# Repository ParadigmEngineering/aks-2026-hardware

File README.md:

# aks-2026-hardware
Autonomous Karting Series (2026) hardware for Paradigm Engineering

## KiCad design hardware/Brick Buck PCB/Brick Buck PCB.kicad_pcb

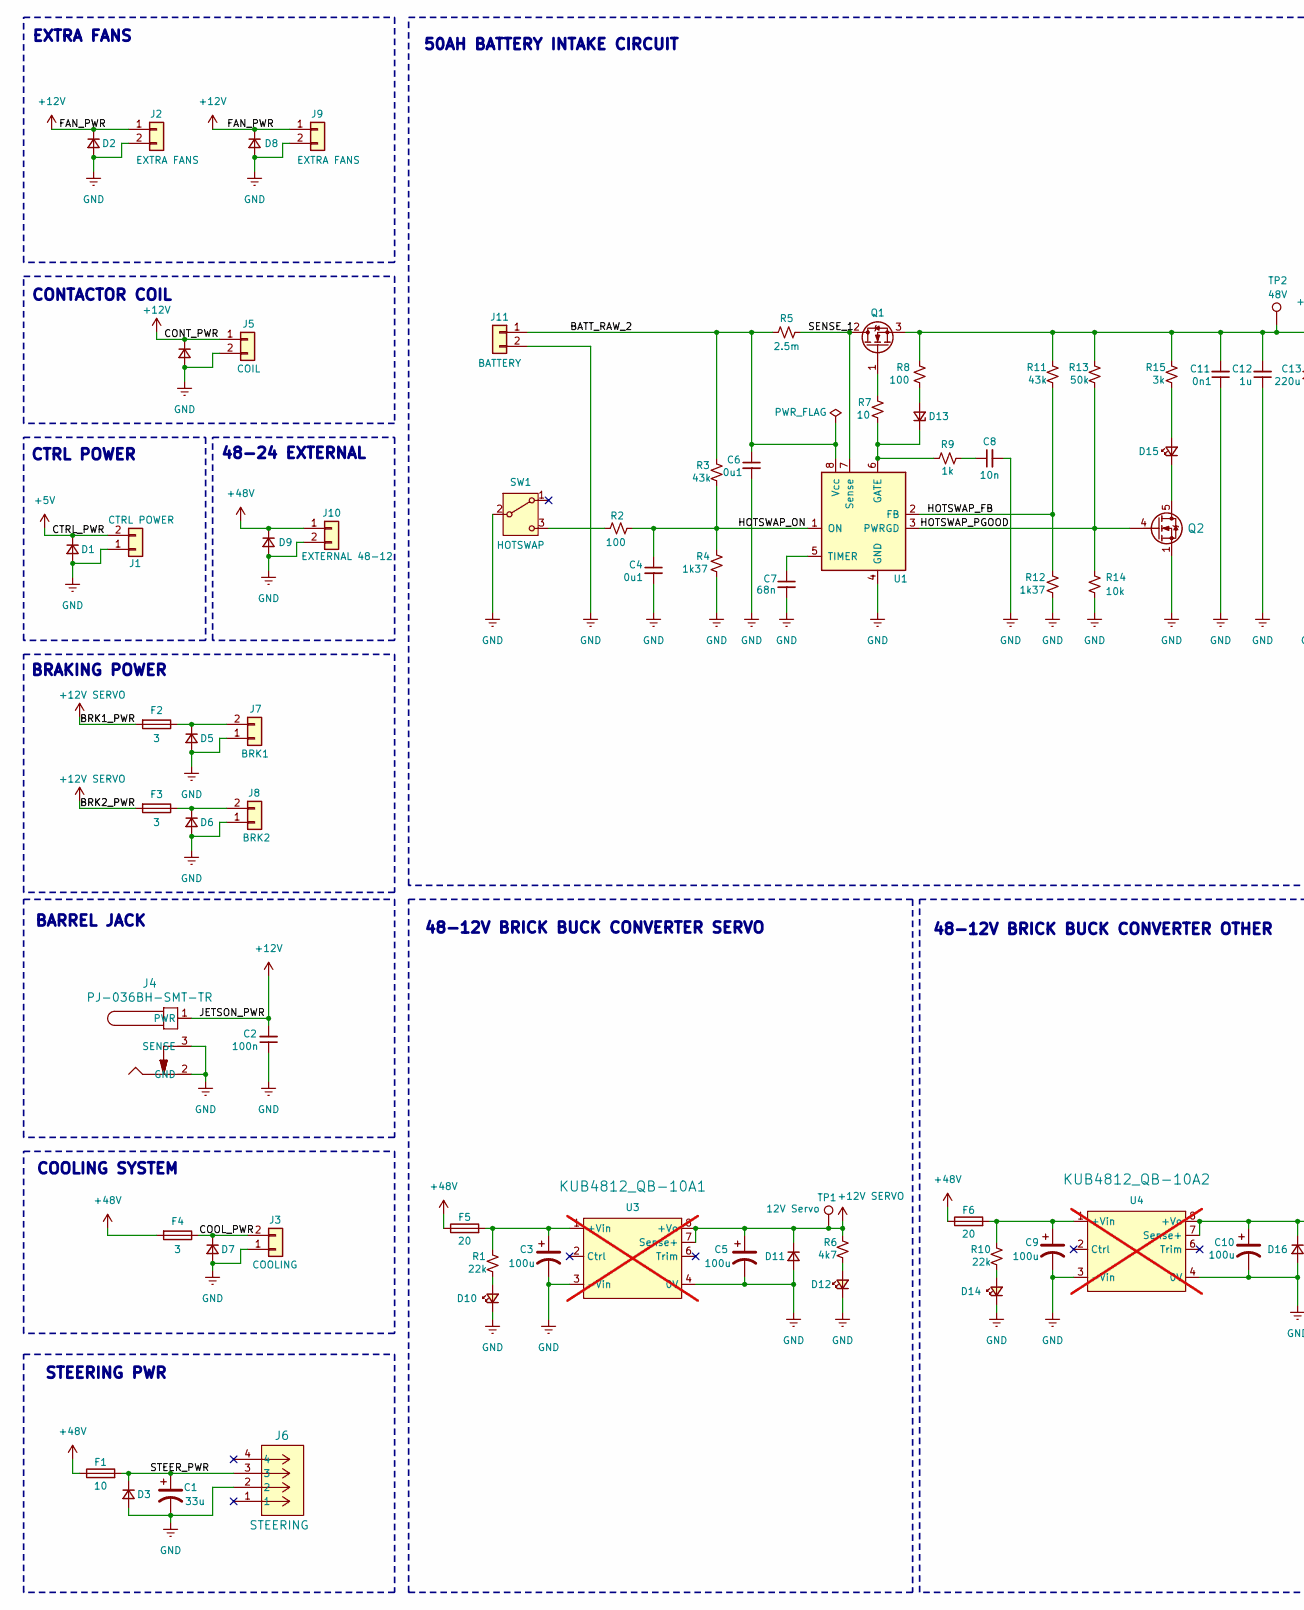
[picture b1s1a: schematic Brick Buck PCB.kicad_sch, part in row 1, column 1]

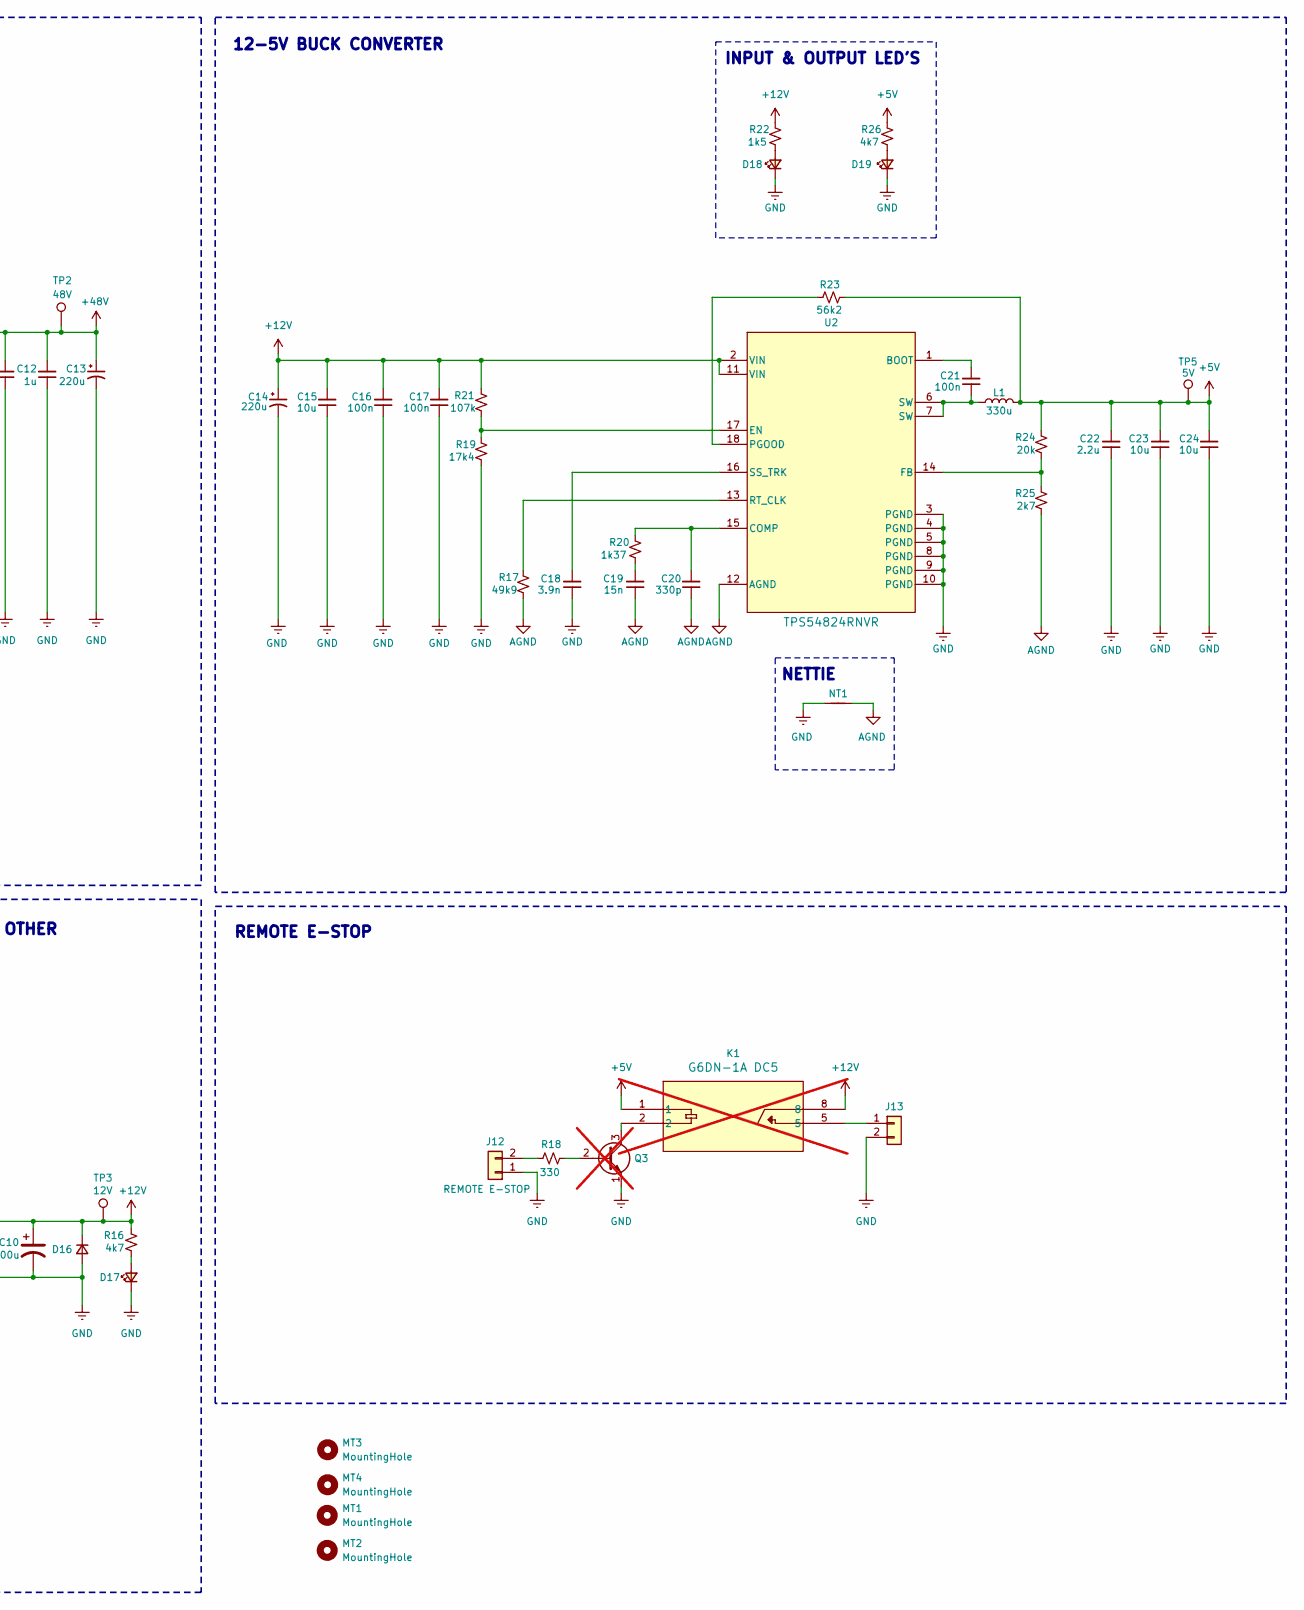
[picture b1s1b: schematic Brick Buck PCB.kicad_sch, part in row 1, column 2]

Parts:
C1: 33u; CP_Radial_D10.0mm_P5.00mm; Digikey 1189-2207-ND
C2: 100n; C_0402_1005Metric_Pad0.74x0.62mm_HandSolder
C3, C9: 100u; CAP_8 X 11.5_PAN
C4, C6: 0u1; C_0805_2012Metric_Pad1.18x1.45mm_HandSolder; Voltage 48V; LCSC 0.1u
C5, C10: 100u; CAPPRD200W50D500H1100
C7: 68n; C_0805_2012Metric_Pad1.18x1.45mm_HandSolder; Voltage 44V; LCSC 68n
C8: 10n; C_0805_2012Metric_Pad1.18x1.45mm_HandSolder; Voltage 68V; LCSC 10n
C11: 0n1; C_0805_2012Metric_Pad1.18x1.45mm_HandSolder; Voltage 48V
C12: 1u; C_0805_2012Metric_Pad1.18x1.45mm_HandSolder; Voltage 48V; LCSC 1u
C13: 220u; CP_Radial_D16.0mm_P7.50mm; Voltage 48V; Digikey 493-5867-ND
C14: 220u; CAPPRD350W60D800H1150
C15: 10u; C_1210_3225Metric_Pad1.33x2.70mm_HandSolder; MANUFACTURER PART NUMBER MSASU32MSB5106KPNA01
C16, C17: 100n; C_0603_1608Metric_Pad1.08x0.95mm_HandSolder; MANUFACTURER PART NUMBER C0603C104M3VACTU
C18: 3.9n; C_0201_0603Metric_Pad0.64x0.40mm_HandSolder; MANUFACTURER PART NUMBER GRM033R71A392KA01D
C19: 15n; C_0805_2012Metric_Pad1.18x1.45mm_HandSolder; MANUFACTURER PART NUMBER GRM2195C1H153JA01D
C20: 330p; C_0402_1005Metric_Pad0.74x0.62mm_HandSolder; MANUFACTURER PART NUMBER GRM1555C1H331JA01D
C21: 100n; C_0402_1005Metric_Pad0.74x0.62mm_HandSolder; MANUFACTURER PART NUMBER GRM155R71C104KA88D
C22: 2.2u; C_0805_2012Metric_Pad1.18x1.45mm_HandSolder; MANUFACTURER PART NUMBER GRM21BR71A225KA01L
C23, C24: 10u; C_0805_2012Metric_Pad1.18x1.45mm_HandSolder; MANUFACTURER PART NUMBER C0805C106K8PACTU
D1, D2, D3, D4, D5, D6, D7, D8, D9: 1655-S1GCT-ND; D_SMA; Digikey S1G
D10, D14, D19: KT-0603R; LED_KT-0603R; PARTREV 2013/01/24
D11, D16: SMDJ14A; DIOM6859X262N
D12, D17, D18: LED; LED_0603_1608Metric
D13: MMSZ5248B-HE3-08; D_SOD-123; Digikey MMSZ5248B-HE3-08GICT-ND
D15: LTST-C171GkT; LED_0805_2012Metric_Pad1.15x1.40mm_HandSolder
F1: 10; 3557-2; Digikey 3557-2
F2, F3, F4: 3; 3557-2; Digikey 36-3557-2-ND
F5, F6: 20; 3557-2
J1: CTRL POWER; Molex_Micro-Fit_3.0_43650-0200_1x02_P3.00mm_Horizontal; Digikey WM1860-ND
J2, J9: EXTRA FANS; Molex_Micro-Fit_3.0_43650-0215_1x02_P3.00mm_Vertical; Digikey WM1917-ND
J3: COOLING; Molex_Micro-Fit_3.0_43650-0200_1x02_P3.00mm_Horizontal; Digikey WM1860-ND
J4: PJ-036BH-SMT-TR; PJ036BHSMTTR
J5: COIL; Molex_Micro-Fit_3.0_43650-0215_1x02_P3.00mm_Vertical; Digikey WM1917-ND
J6: STEERING; CONN_SD-46207-001_04_MOL
J7: BRK1; Molex_Micro-Fit_3.0_43650-0200_1x02_P3.00mm_Horizontal; Digikey WM1860-ND
J8: BRK2; Molex_Micro-Fit_3.0_43650-0200_1x02_P3.00mm_Horizontal; Digikey WM1860-ND
J10: EXTERNAL 48-12; Molex_Micro-Fit_3.0_43650-0215_1x02_P3.00mm_Vertical; Digikey WM1917-ND
J11: BATTERY; Molex_Mini-Fit_Sr_42820-22XX_1x02_P10.00mm_Horizontal; Digikey WM11250-ND
J12: REMOTE E-STOP; Molex_KK-254_AE-6410-02A_1x02_P2.54mm_Vertical
J13: Conn_01x02; Molex_Micro-Fit_3.0_43650-0215_1x02_P3.00mm_Vertical
K1: G6DN-1A DC5; RELAY_G6DN-1A_OMR; not fitted
KUB4812_QB-10A1: U3; KUB48_QB-10A; not fitted
KUB4812_QB-10A2: U4; KUB48_QB-10A; not fitted
L1: 330u; SRN8040-3R3Y; Manufacturer_Part_Number SRN8040-3R3Y; Mouser Part Number 652-SRN8040-3R3Y
MT1, MT2, MT3, MT4: MountingHole; MountingHole_3.2mm_M3
NT1: NetTie1; NetTie-2_THT_Pad0.3mm
Q1: CSD19506KTT; TO-263-2; Digikey 296-49604-1-ND
Q2: CSD18543Q3A; VSON-8_3.3x3.3mm_P0.65mm_NexFET
Q3: 2N7000; TO92254P458H750-3; not fitted
R1, R10: 22k; R_0805_2012Metric_Pad1.20x1.40mm_HandSolder
R2, R8: 100; R_0805_2012Metric_Pad1.20x1.40mm_HandSolder; LCSC 100
R3, R11: 43k; R_0805_2012Metric_Pad1.20x1.40mm_HandSolder; LCSC 43K
R4, R12: 1k37; R_0805_2012Metric_Pad1.20x1.40mm_HandSolder; LCSC 1.37K
R5: 2.5m; R_2512_6332Metric_Pad1.40x3.35mm_HandSolder; Digikey_2.5m WSLF25121L300FEA
R6, R16, R26: 4k7; R_0805_2012Metric_Pad1.20x1.40mm_HandSolder
R7: 10; R_0805_2012Metric_Pad1.20x1.40mm_HandSolder; LCSC 10
R9: 1k; R_0805_2012Metric_Pad1.20x1.40mm_HandSolder; LCSC 1K
R13: 50k; R_0805_2012Metric_Pad1.20x1.40mm_HandSolder; LCSC 50k
R14: 10k; R_0805_2012Metric_Pad1.20x1.40mm_HandSolder; LCSC 10k
R15: 3k; R_0805_2012Metric_Pad1.20x1.40mm_HandSolder; LCSC 3k
R17: 49k9; R_0402_1005Metric_Pad0.72x0.64mm_HandSolder; MANUFACTURER PART NUMBER CRCW040249K9FKED
R18: 330; R_0402_1005Metric
R19: 17k4; R_0603_1608Metric_Pad0.98x0.95mm_HandSolder; MANUFACTURER PART NUMBER FRC0603F1742TS
R20: 1k37; R_0402_1005Metric_Pad0.72x0.64mm_HandSolder; MANUFACTURER PART NUMBER CRCW04021K37FKED
R21: 107k; R_0603_1608Metric_Pad0.98x0.95mm_HandSolder; MANUFACTURER PART NUMBER CRCW0402107KFKED
R22: 1k5; R_0805_2012Metric_Pad1.20x1.40mm_HandSolder
R23: 56k2; R_0402_1005Metric_Pad0.72x0.64mm_HandSolder; MANUFACTURER PART NUMBER RT0402FRE0756K2L
R24: 20k; R_0603_1608Metric_Pad0.98x0.95mm_HandSolder; MANUFACTURER PART NUMBER CRCW040220K0FKED
R25: 2k7; R_0603_1608Metric_Pad0.98x0.95mm_HandSolder; MANUFACTURER PART NUMBER CRCW04022K74FKED
SW1: HOTSWAP; SW_EG1218; Digikey EG1903-ND
TP1: 12V Servo; TestPoint_Pad_D2.5mm
TP2: 48V; TestPoint_Pad_D2.5mm
TP3: 12V; TestPoint_Pad_D2.5mm
TP5: 5V; TestPoint_Pad_D2.5mm
U1: LT1641-1CS8#TRPBF; SOIC-8_3.9x4.9mm_P1.27mm; Digikey LT1641-1
U2: TPS54824RNVR; RNV0018B

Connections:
+5V: C22.2, C23.2, C24.2, D1.1 (K), J1.2, K1.1, L1.2, R23.2, R24.2, R26.2, TP5.1; also elsewhere on the board
+12V: C2.2, C10.P, C14.P, C15.2, C16.2, C17.2, D2.1 (K), D4.1 (K), D8.1 (K), D16.C (K), J2.1, J4.1 (PWR), J5.1, J9.1, K1.8, KUB4812_QB-10A2.7 (Sense+), KUB4812_QB-10A2.8 (+Vo), R16.2, R21.1, R22.1, TP3.1 (1_1), U2.2 (VIN), U2.11 (VIN)
+12V SERVO: C5.P, D11.C (K), F2.2, F3.2, KUB4812_QB-10A1.7 (Sense+), KUB4812_QB-10A1.8 (+Vo), R6.2, TP1.1 (1_1)
+48V: C11.2, C12.2, C13.1, D9.1 (K), F1.1, F4.2, F5.1, F6.1, J10.1, Q1.3 (S), R8.2, R11.1, R13.1, R15.1, TP2.1 (1_1)
/BATT_RAW_2: C6.1, J11.1, R3.1, R5.2, U1.8 (Vcc)
/COOL_PWR: D7.1 (K), F4.1, J3.2
/HOTSWAP_FB: R11.2, R12.1, U1.2 (FB)
/HOTSWAP_ON: C4.1, R2.1, R3.2, R4.1, U1.1 (ON)
/HOTSWAP_PGOOD: Q2.4 (G), R13.2, R14.1, U1.3 (PWRGD)
/SENSE_1: Q1.2 (D), R5.1, U1.7 (Sense)
/STEER_PWR: C1.1, D3.1 (K), F1.2, J6.3
AGND: C19.1, C20.1, NT1.2, R17.1, R25.1, U2.12 (AGND)
GND: C1.2, C2.1, C3.2, C4.2, C5.N, C6.2, C7.2, C8.2, C9.2, C10.N, C11.1, C12.1, C13.2, C14.N, C15.1, C16.1, C17.1, C18.1, C22.1, C23.1, C24.1, D1.2 (A), D2.2 (A), D3.2 (A), D4.2 (A), D5.2 (A), D6.2 (A), D7.2 (A), D8.2 (A), D9.2 (A), D10.C (K), D11.A, D12.1 (K), D14.C (K), D16.A, D17.1 (K), D18.1 (K), D19.C (K), J1.1, J2.2, J3.1, J4.2 (GND), J4.3 (SENSE), J5.2, J6.2, J7.1, J8.1, J9.2, J10.2, J11.2, J12.1, J13.2, KUB4812_QB-10A1.3 (-Vin), KUB4812_QB-10A1.4 (0V), KUB4812_QB-10A2.3 (-Vin), KUB4812_QB-10A2.4 (0V), NT1.1, Q2.1 (S), Q2.2 (S), Q2.3 (S), Q3.1 (E), R4.2, R12.2, R14.2, R19.2, SW1.2 (B), U1.4 (GND), U2.3 (PGND), U2.4 (PGND), U2.5 (PGND), U2.8 (PGND), U2.9 (PGND), U2.10 (PGND)
unnamed: C8.1, R9.1
unnamed: C19.2, R20.1
unnamed: C21.1, L1.1, U2.6 (SW), U2.7 (SW)
unnamed: D5.1 (K), F2.1, J7.2
unnamed: D6.1 (K), F3.1, J8.2
unnamed: D10.A, R1.1
unnamed: D12.2 (A), R6.1
unnamed: D13.2 (A), R8.1
unnamed: D13.1 (K), R7.2, R9.2, U1.6 (GATE)
unnamed: D14.A, R10.1
unnamed: D15.2 (A), R15.2
unnamed: D15.1 (K), Q2.5 (D)
unnamed: D17.2 (A), R16.1
unnamed: D18.2 (A), R22.2
unnamed: D19.A, R26.1
unnamed: J12.2, R18.1
unnamed: J13.1, K1.5
unnamed: C3.1, F5.2, KUB4812_QB-10A1.1 (+Vin), R1.2
unnamed: C9.1, F6.2, KUB4812_QB-10A2.1 (+Vin), R10.2
unnamed: Q1.1 (G), R7.1
unnamed: Q3.2 (B), R18.2
unnamed: K1.2, Q3.3 (C)
unnamed: R2.2, SW1.3 (C)
unnamed: C7.1, U1.5 (TIMER)
unnamed: C21.2, U2.1 (BOOT)
unnamed: C20.2, R20.2, U2.15 (COMP)
unnamed: R19.1, R21.2, U2.17 (EN)
unnamed: R24.1, R25.2, U2.14 (FB)
unnamed: R23.1, U2.18 (PGOOD)
unnamed: R17.2, U2.13 (RT_CLK)
unnamed: C18.2, U2.16 (SS_TRK)

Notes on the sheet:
NETTIE
50AH BATTERY INTAKE CIRCUIT
CTRL POWER
48-12V BRICK BUCK CONVERTER SERVO
BARREL JACK
INPUT & OUTPUT LED'S
48-24 EXTERNAL
48-12V BRICK BUCK CONVERTER OTHER
CONTACTOR COIL
REMOTE E-STOP
COOLING SYSTEM
12-5V BUCK CONVERTER
BRAKING POWER
EXTRA FANS
STEERING PWR

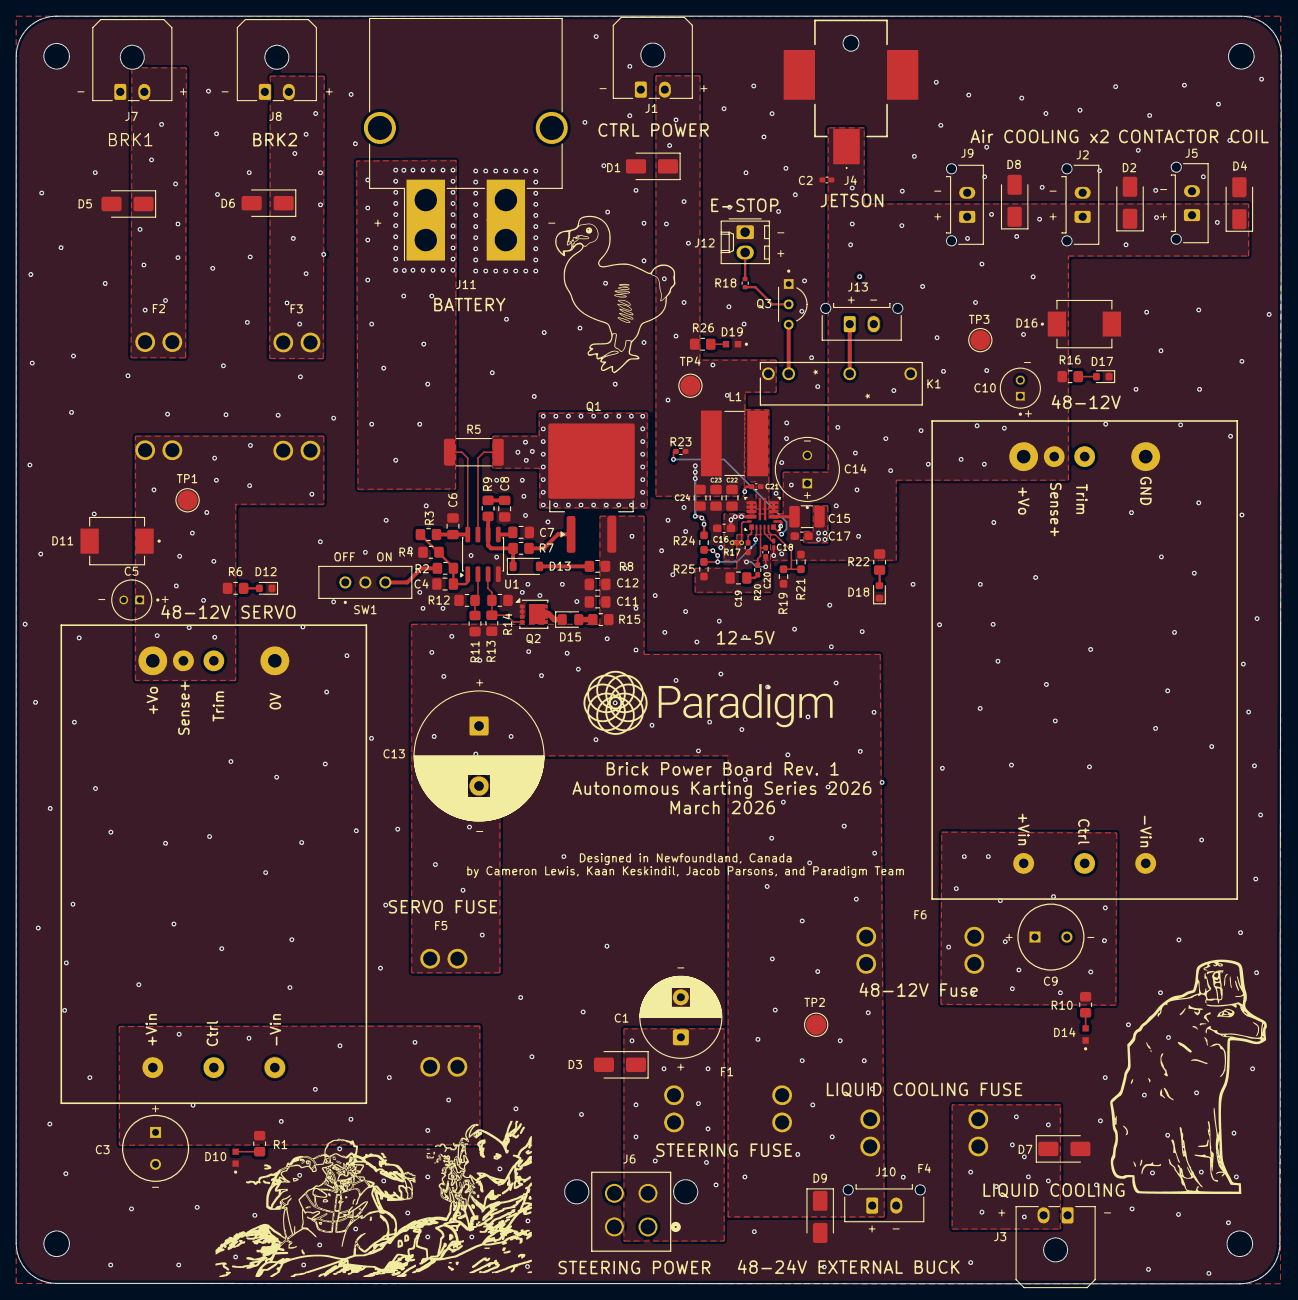
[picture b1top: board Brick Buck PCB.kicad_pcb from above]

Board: 4 copper layers, 158.0 x 158.3 mm, 107 parts (0 on the bottom side), 44 nets.

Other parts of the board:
TP4: 5V; TestPoint_Pad_D2.5mm

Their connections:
+5V: TP4.1 (1_1); also elsewhere on the board

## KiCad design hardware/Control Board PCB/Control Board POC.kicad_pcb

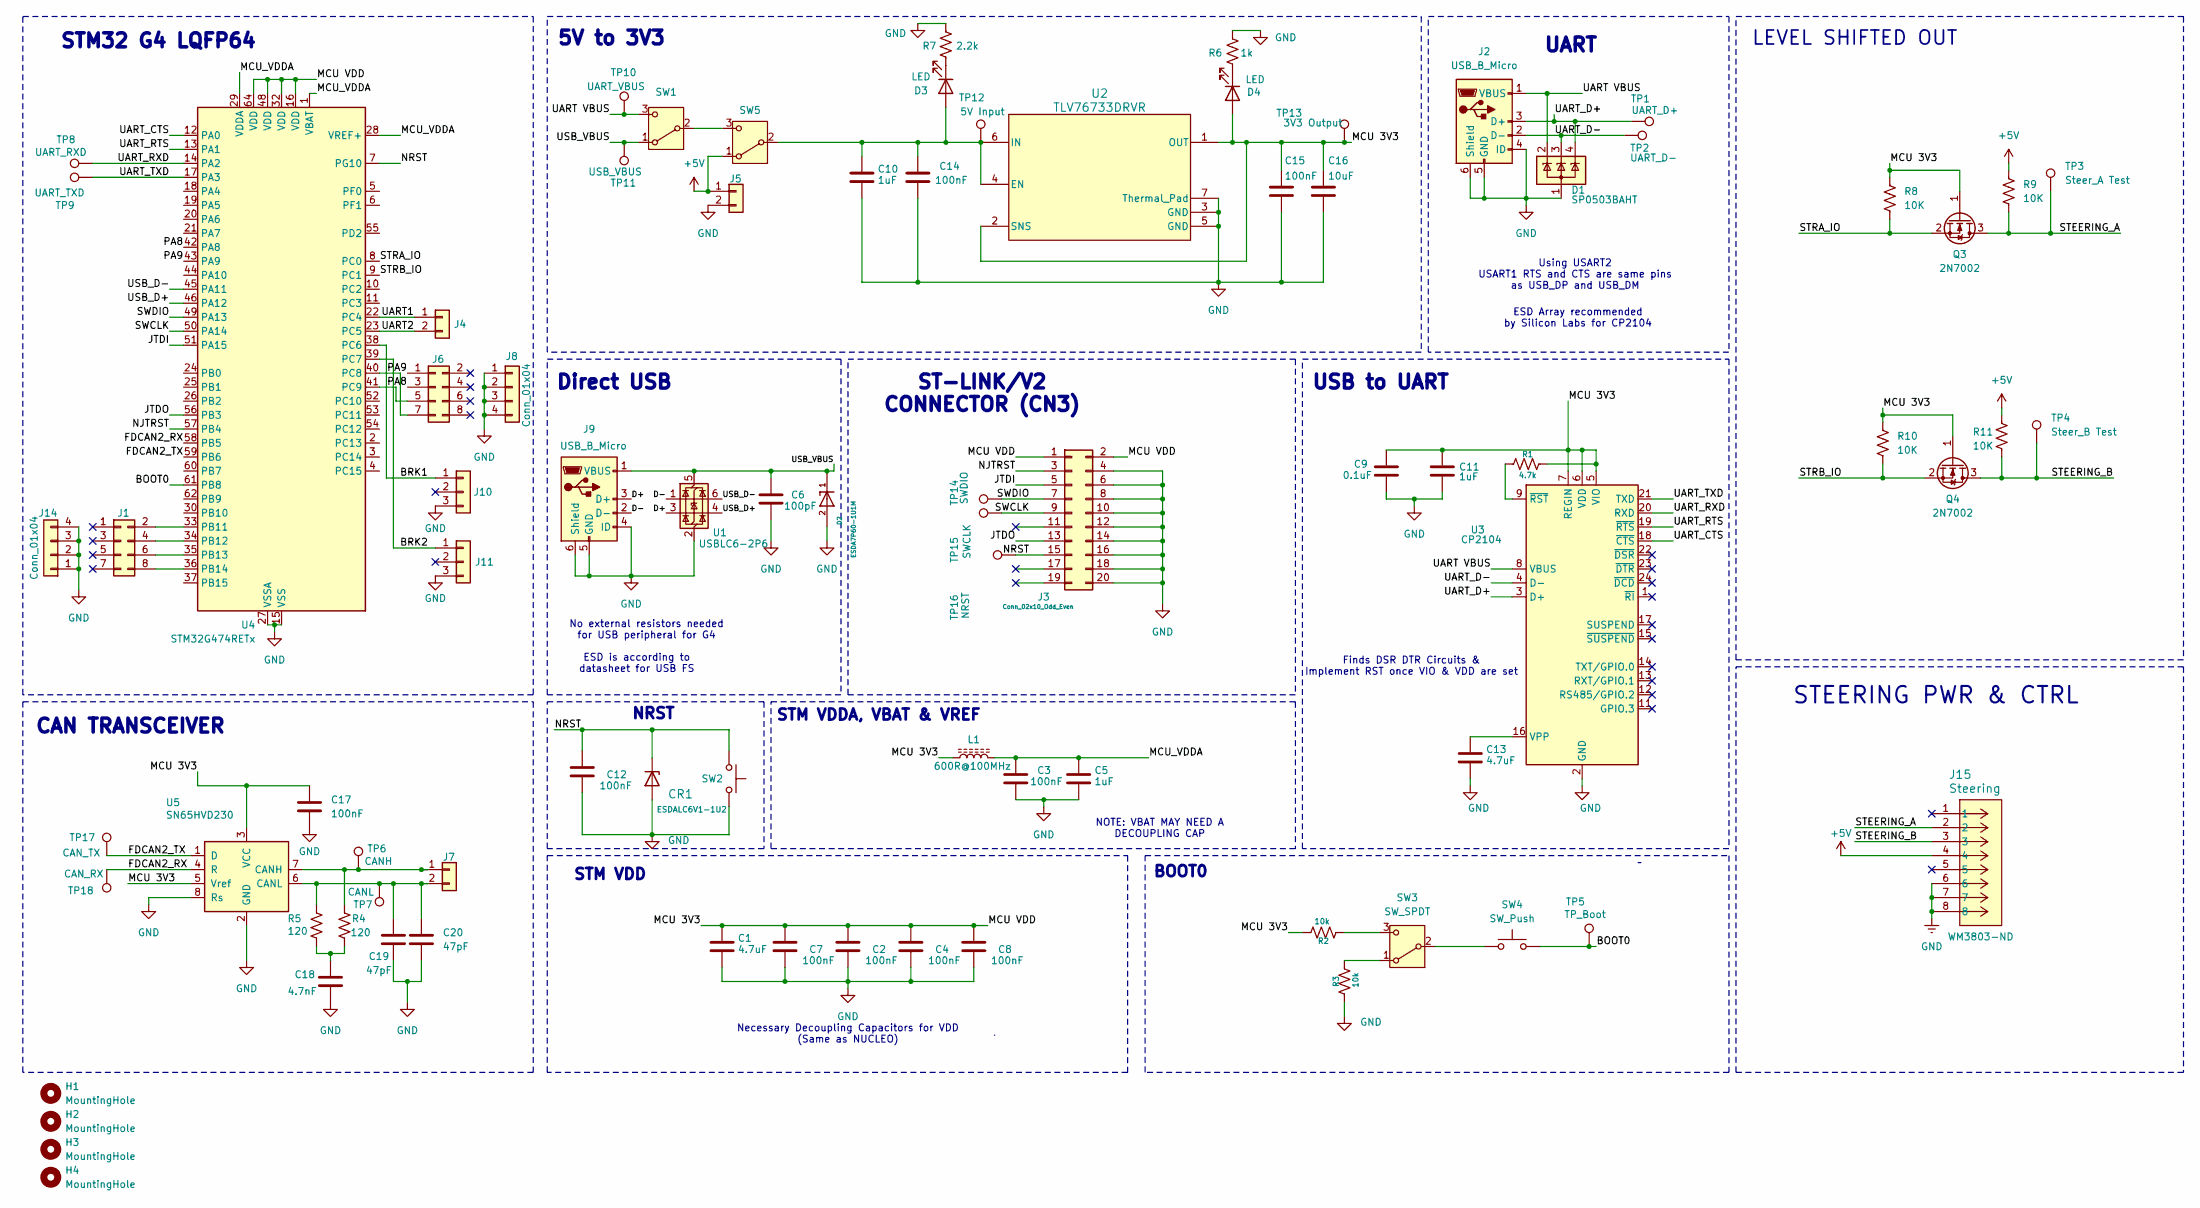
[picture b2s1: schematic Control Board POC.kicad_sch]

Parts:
C1, C13: 4.7uF; C_0402_1005Metric_Pad0.74x0.62mm_HandSolder
C2, C3, C4, C7, C8, C12, C14, C15: 100nF; C_0402_1005Metric_Pad0.74x0.62mm_HandSolder
C5, C10, C11: 1uF; C_0402_1005Metric_Pad0.74x0.62mm_HandSolder
C6: 100pF; C_0402_1005Metric_Pad0.74x0.62mm_HandSolder
C9: 0.1uF; C_0402_1005Metric_Pad0.74x0.62mm_HandSolder
C16: 10uF; C_0402_1005Metric_Pad0.74x0.62mm_HandSolder
C17: 100nF; C_0402_1005Metric
C18: 4.7nF; C_0402_1005Metric
C19, C20: 47pF; C_0402_1005Metric
CR1: ESDALC6V1-1U2; DIODE_ESDALC6V1-1U2
D1: SP0503BAHT; SOT-143
D2: ESDA7P60-1U1M; TVS_ESDA7P60-1U1M; PARTREV 4
D3: LED; LED_0603_1608Metric
D4: LED; LED_0805_2012Metric
H1, H2, H3, H4: MountingHole; MountingHole_3.2mm_M3
J1, J6: Conn_02x04_Odd_Even; PinHeader_2x04_P2.54mm_Vertical
J2, J9: USB_B_Micro; USB_Micro-B_Amphenol_10118194_Horizontal
J3: Conn_02x10_Odd_Even; PinHeader_2x10_P2.54mm_Vertical
J4, J5: Conn_01x02; PinHeader_1x02_P2.54mm_Vertical
J7: Conn_01x02; CONN_SD-43650-010_02_MOL
J8, J14: Conn_01x04; PinHeader_1x04_P2.54mm_Vertical
J10, J11: Conn_01x03; PinHeader_1x03_P2.54mm_Vertical
J15: Steering; CONN_5566-08_MOL; Digikey WM3803-ND
L1: 600R@100MHz; L_0805_2012Metric
Q3, Q4: 2N7002; SOT-23
R1: 4.7k; R_0201_0603Metric
R2, R3: 10k; R_0201_0603Metric
R4, R5: 120; R_0201_0603Metric
R6: 1k; R_0201_0603Metric
R7: 2.2k; R_0201_0603Metric
R8, R9, R10, R11: 10K; R_0805_2012Metric_Pad1.20x1.40mm_HandSolder
SW1, SW3, SW5: SW_SPDT; SW_EG1218
SW2, SW4: SW_Push; PTS636SK25FSMTRLFS
TP1: UART_D+; TestPoint_Pad_D1.0mm
TP2: UART_D-; TestPoint_Pad_D1.0mm
TP3: Steer_A Test; TestPoint_Pad_D1.0mm
TP4: Steer_B Test; TestPoint_Pad_D1.0mm
TP5: TP_Boot; TestPoint_Pad_D1.0mm
TP6: CANH; TestPoint_Pad_D1.0mm
TP7: CANL; TestPoint_Pad_D1.0mm
TP8: UART_RXD; TestPoint_Pad_D1.0mm
TP9: UART_TXD; TestPoint_Pad_D1.0mm
TP10: UART_VBUS; TestPoint_Pad_D1.0mm
TP11: USB_VBUS; TestPoint_Pad_D1.0mm
TP12: 5V Input; TestPoint_Pad_D1.0mm
TP13: 3V3 Output; TestPoint_Pad_D1.0mm
TP14: SWDIO; TestPoint_Pad_D1.0mm
TP15: SWCLK; TestPoint_Pad_D1.0mm
TP16: NRST; TestPoint_Pad_D1.0mm
TP17: CAN_TX; TestPoint_Pad_D1.0mm
TP18: CAN_RX; TestPoint_Pad_D1.0mm
U1: USBLC6-2P6; SOT-666
U2: TLV76733DRVR; DRV0006A-IPC_B
U3: CP2104; QFN-24-1EP_4x4mm_P0.5mm_EP2.6x2.6mm
U4: STM32G474RETx; LQFP-64_10x10mm_P0.5mm
U5: SN65HVD230; SOIC-8_3.9x4.9mm_P1.27mm

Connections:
+5V: J5.1, J15.4, R9.1, R11.1, SW5.1 (A)
/BOOT0: SW4.2, TP5.1, U4.61 (PB8)
/BRK1: J10.1, U4.38 (PC6)
/BRK2: J11.1, U4.39 (PC7)
/D+: J9.3 (D+), U1.3 (I/O2)
/D-: J9.2 (D-), U1.1 (I/O1)
/FDCAN2_RX: TP18.1, U4.58 (PB5), U5.4 (R)
/FDCAN2_TX: TP17.1, U4.59 (PB6), U5.1 (D)
/JTDI: J3.5, U4.51 (PA15)
/JTDO: J3.13, U4.56 (PB3)
/MCU 3V3: C1.1, C2.1, C4.1, C7.1, C8.1, C9.2, C11.1, C15.1, C16.1, C17.1, D4.2 (A), J3.1, J3.2, L1.1, Q3.1 (G), Q4.1 (G), R1.2, R2.2, R8.1, R10.1, TP13.1, U2.1 (OUT), U2.2 (SNS), U3.5 (VIO), U3.6 (VDD), U3.7 (REGIN), U4.16 (VDD), U4.32 (VDD), U4.48 (VDD), U4.64 (VDD), U5.3 (VCC), U5.5 (Vref)
/MCU_VDDA: C3.1, C5.1, L1.2, U4.1 (VBAT), U4.28 (VREF+), U4.29 (VDDA)
/NJTRST: J3.3, U4.57 (PB4)
/NRST: C12.1, CR1.1 (K), J3.15, SW2.1, TP16.1, U4.7 (PG10)
/PA8: J6.3, U4.42 (PA8)
/PA9: J6.1, U4.43 (PA9)
/STEERING_A: J15.2, Q3.3 (D), R9.2, TP3.1
/STEERING_B: J15.3, Q4.3 (D), R11.2, TP4.1
/STRA_IO: Q3.2 (S), R8.2, U4.8 (PC0)
/STRB_IO: Q4.2 (S), R10.2, U4.9 (PC1)
/SWCLK: J3.9, TP15.1, U4.50 (PA14)
/SWDIO: J3.7, TP14.1, U4.49 (PA13)
/UART1: J4.1, U4.22 (PC4)
/UART2: J4.2, U4.23 (PC5)
/UART VBUS: D1.2 (K), J2.1 (VBUS), SW1.3 (C), TP10.1, U3.8 (VBUS)
/UART_CTS: U3.18 (~CTS), U4.12 (PA0)
/UART_D+: D1.4 (K), J2.3 (D+), TP1.1, U3.3 (D+)
/UART_D-: D1.3 (K), J2.2 (D-), TP2.1, U3.4 (D-)
/UART_RTS: U3.19 (~RTS), U4.13 (PA1)
/UART_RXD: TP8.1, U3.20 (RXD), U4.14 (PA2)
/UART_TXD: TP9.1, U3.21 (TXD), U4.17 (PA3)
/USB_D+: U1.4 (I/O2), U4.46 (PA12)
/USB_D-: U1.6 (I/O1), U4.45 (PA11)
/USB_VBUS: C6.1, D2.1, J9.1 (VBUS), SW1.1 (A), TP11.1, U1.5 (VBUS)
GND: C1.2, C2.2, C3.2, C4.2, C5.2, C6.2, C7.2, C8.2, C9.1, C10.2, C11.2, C12.2, C13.2, C14.2, C15.2, C16.2, C17.2, C18.2, C19.2, C20.2, CR1.2 (A), D1.1 (A), D2.2, J2.4 (ID), J2.5 (GND), J2.6 (Shield), J3.4, J3.6, J3.8, J3.10, J3.12, J3.14, J3.16, J3.18, J3.20, J5.2, J8.1, J8.2, J8.3, J8.4, J9.4 (ID), J9.5 (GND), J9.6 (Shield), J10.3, J11.3, J14.1, J14.2, J14.3, J14.4, J15.6, J15.7, J15.8, R3.1, R6.2, R7.1, SW2.2, U1.2 (GND), U2.3 (GND), U2.5 (GND), U2.7 (Thermal_Pad), U3.2 (GND), U3.25 (GND), U4.15 (VSS), U4.27 (VSSA), U4.31 (VSS), U4.47 (VSS), U4.63 (VSS), U5.2 (GND), U5.8 (Rs)
unnamed: C18.1, R4.2, R5.2
unnamed: C10.1, C14.1, D3.2 (A), SW5.2 (B), TP12.1, U2.4 (EN), U2.6 (IN)
unnamed: D3.1 (K), R7.2
unnamed: D4.1 (K), R6.1
unnamed: J1.2, U4.33 (PB11)
unnamed: J1.4, U4.34 (PB12)
unnamed: J1.6, U4.35 (PB13)
unnamed: J1.8, U4.36 (PB14)
unnamed: J6.5, U4.41 (PC9)
unnamed: J6.7, U4.40 (PC8)
unnamed: J7.1, R4.1, TP6.1, U5.7 (CANH)
unnamed: C19.1, C20.1, J7.2, R5.1, TP7.1, U5.6 (CANL)
unnamed: SW1.2 (B), SW5.3 (C)
unnamed: R3.2, SW3.1 (A)
unnamed: SW3.2 (B), SW4.1
unnamed: R2.1, SW3.3 (C)
unnamed: C13.1, U3.16 (VPP)
unnamed: R1.1, U3.9 (~RST)

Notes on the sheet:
Direct USB
STM VDD
Necessary Decoupling Capacitors for VDD (Same as NUCLEO)
5V to 3V3
LEVEL SHIFTED OUT
ESD Array recommended by Silicon Labs for CP2104
Using USART2 USART1 RTS and CTS are same pins as USB_DP and USB_DM
USB to UART
STM VDDA, VBAT & VREF
STEERING PWR & CTRL
BOOT0
ESD is according to datasheet for USB FS
ST-LINK/V2 CONNECTOR (CN3)
Finds DSR DTR Circuits & Implement RST once VIO & VDD are set
No external resistors needed for USB peripheral for G4
STM32 G4 LQFP64
CAN TRANSCEIVER
NRST
UART
NOTE: VBAT MAY NEED A DECOUPLING CAP

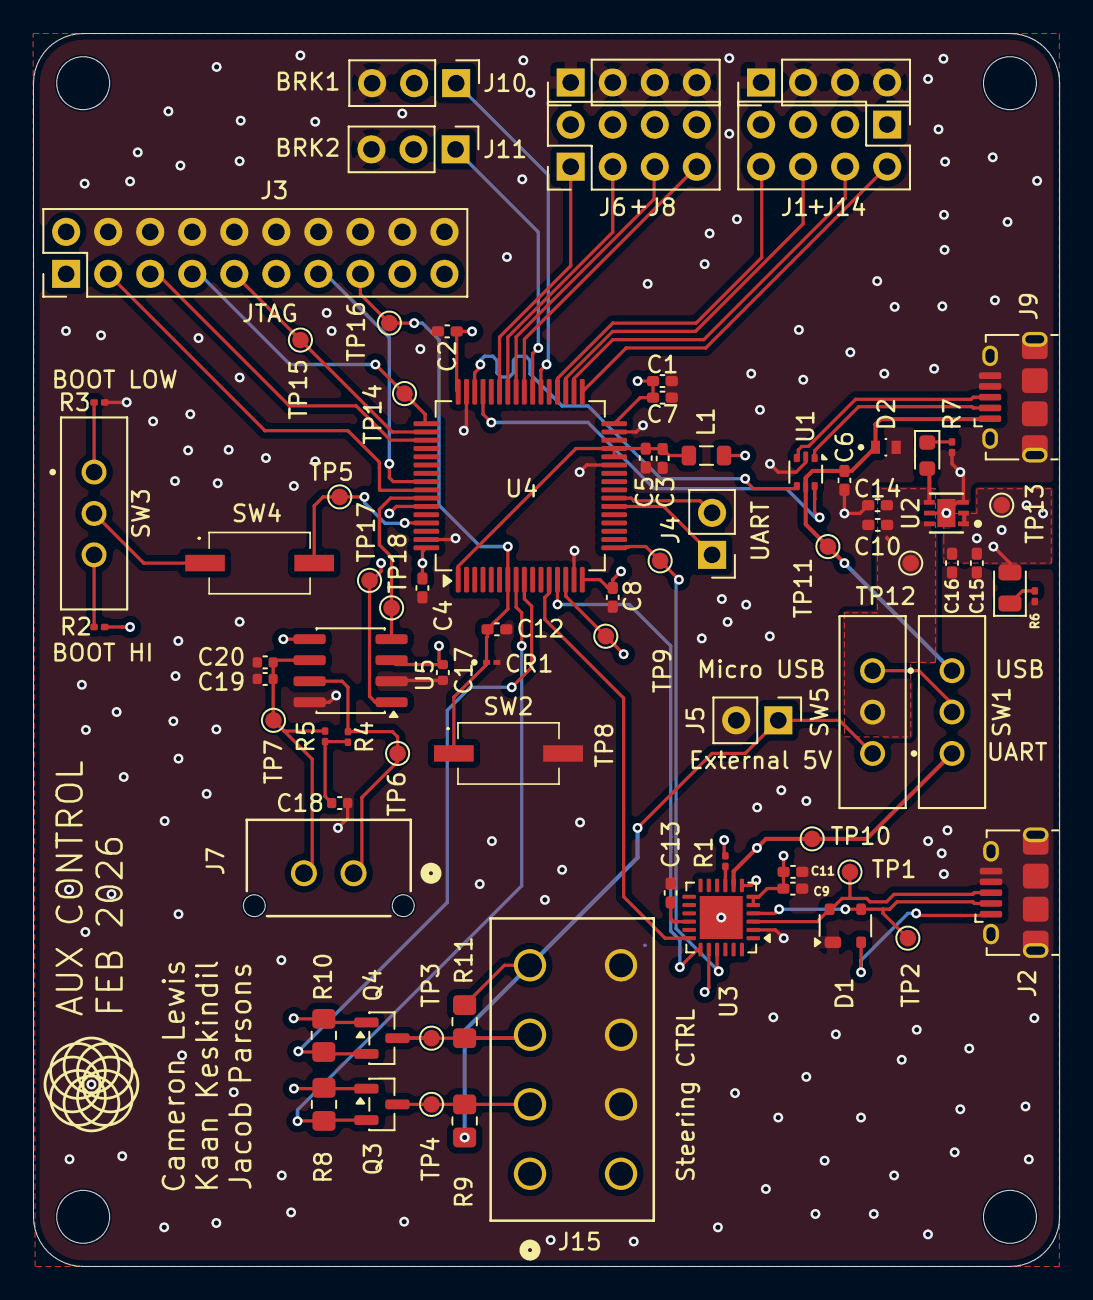
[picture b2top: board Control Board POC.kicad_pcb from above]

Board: 4 copper layers, 62.0 x 74.5 mm, 84 parts (0 on the bottom side), 53 nets.

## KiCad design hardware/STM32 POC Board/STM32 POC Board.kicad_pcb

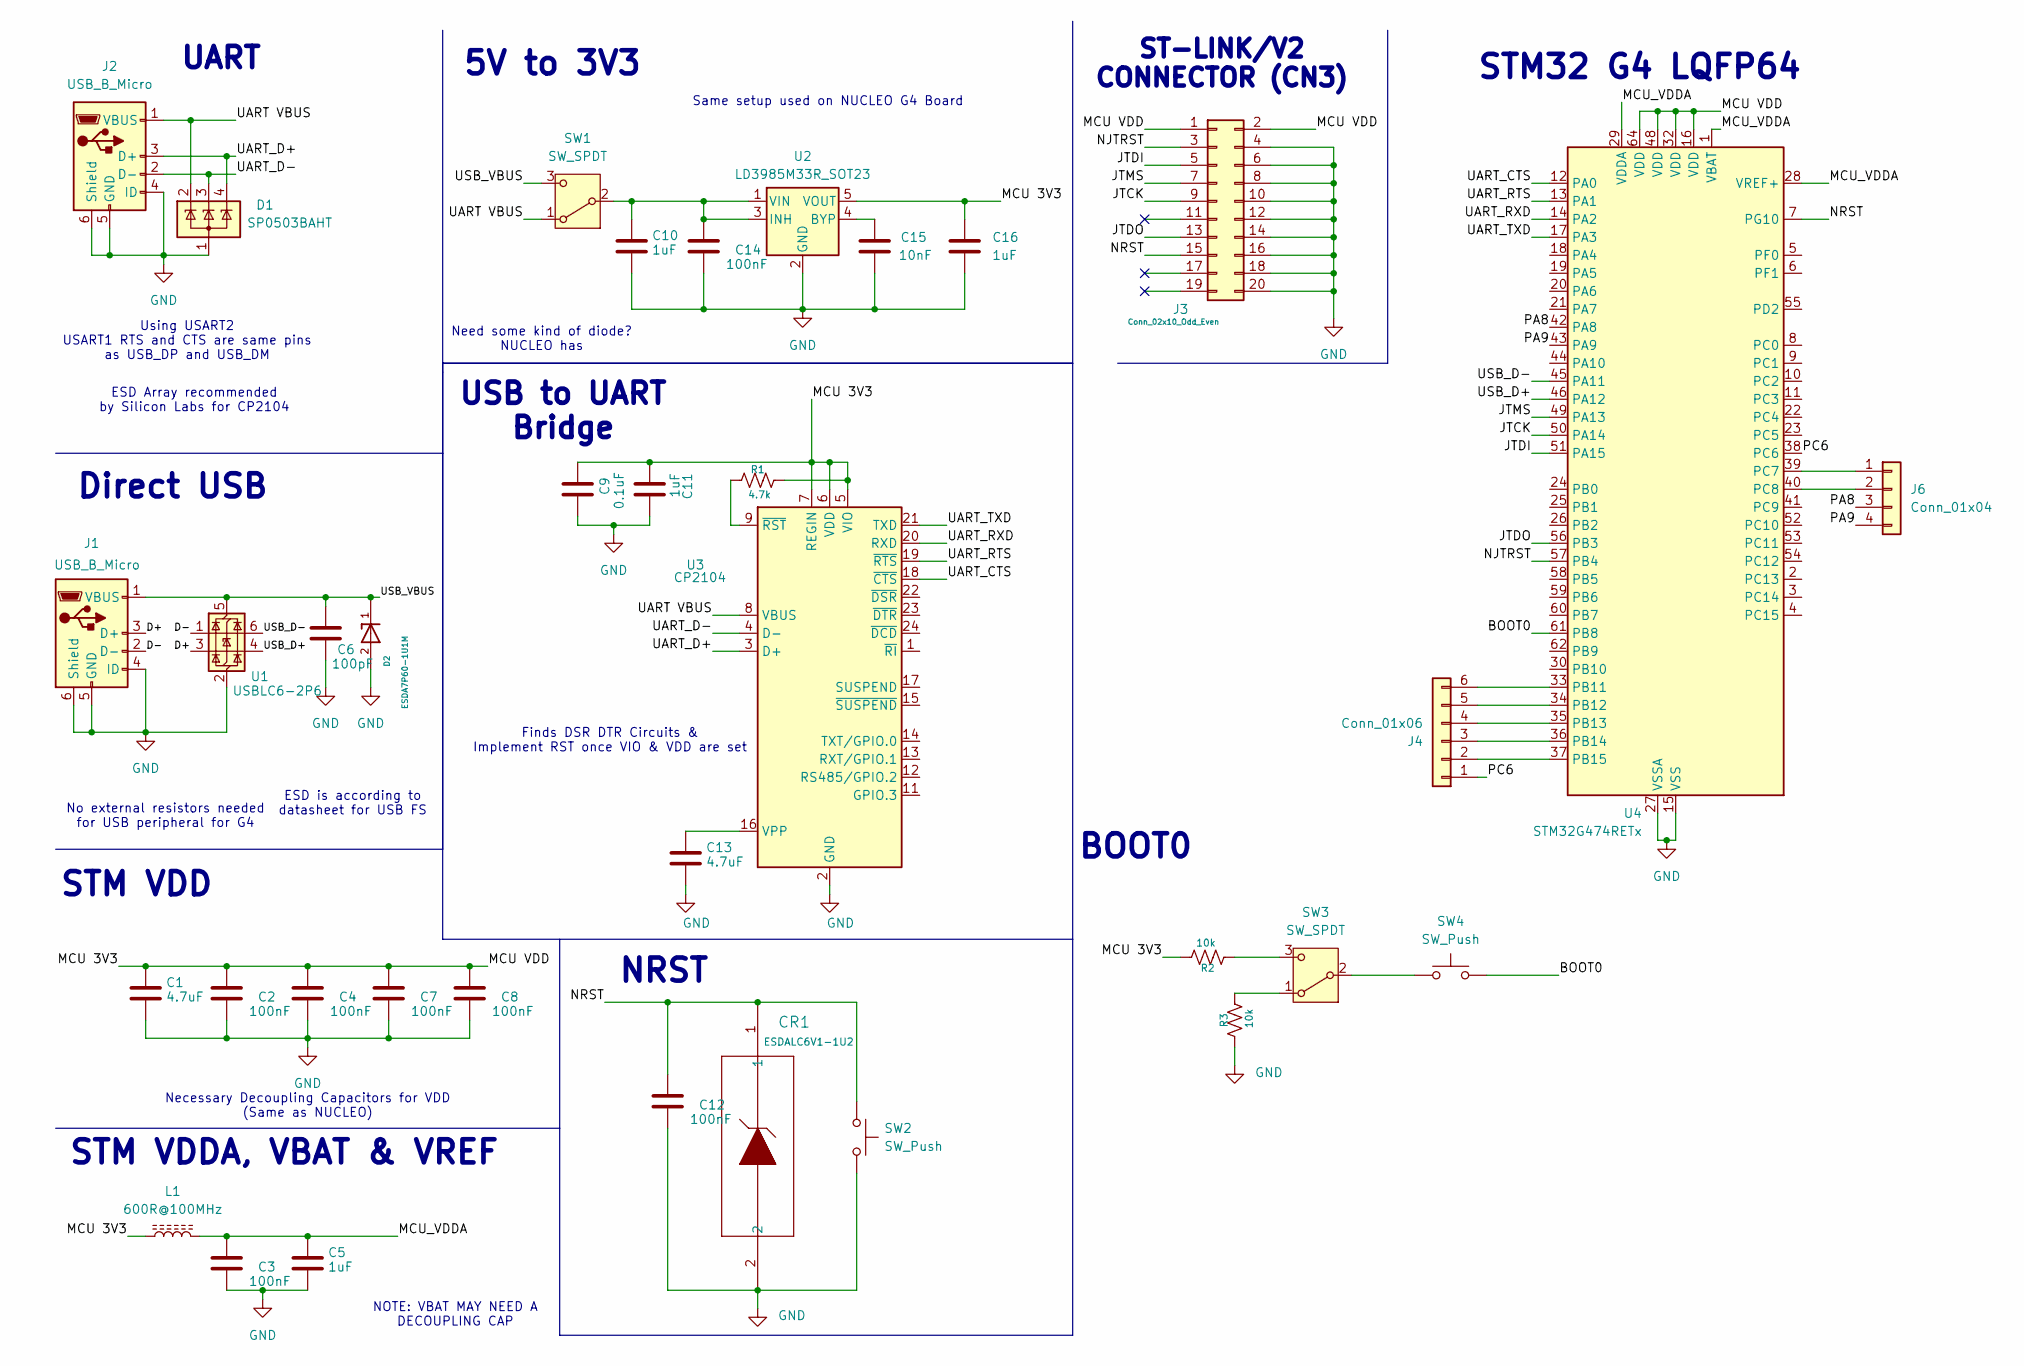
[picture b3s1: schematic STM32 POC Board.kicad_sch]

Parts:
C1, C13: 4.7uF; C_0402_1005Metric_Pad0.74x0.62mm_HandSolder
C2, C3, C4, C7, C8, C12, C14: 100nF; C_0402_1005Metric_Pad0.74x0.62mm_HandSolder
C5, C10, C11, C16: 1uF; C_0402_1005Metric_Pad0.74x0.62mm_HandSolder
C6: 100pF; C_0402_1005Metric_Pad0.74x0.62mm_HandSolder
C9: 0.1uF; C_0402_1005Metric_Pad0.74x0.62mm_HandSolder
C15: 10nF; C_0402_1005Metric_Pad0.74x0.62mm_HandSolder
CR1: ESDALC6V1-1U2; DIODE_ESDALC6V1-1U2
D1: SP0503BAHT; SOT-143
D2: ESDA7P60-1U1M; TVS_ESDA7P60-1U1M; PARTREV 4
J1, J2: USB_B_Micro; USB_Micro-B_Amphenol_10118194_Horizontal
J3: Conn_02x10_Odd_Even; PinHeader_2x10_P2.54mm_Vertical
J4: Conn_01x06; PinHeader_1x06_P2.54mm_Vertical
J6: Conn_01x04; PinHeader_1x04_P2.54mm_Vertical
L1: 600R@100MHz; L_0805_2012Metric
R1: 4.7k; R_0201_0603Metric
R2, R3: 10k; R_0201_0603Metric
SW1, SW3: SW_SPDT; 3A_SW
SW2, SW4: SW_Push; PTS636SP50SMTRLFS
U1: USBLC6-2P6; SOT-666
U2: LD3985M33R_SOT23; SOT-23-5
U3: CP2104; QFN-24-1EP_4x4mm_P0.5mm_EP2.6x2.6mm
U4: STM32G474RETx; LQFP-64_10x10mm_P0.5mm

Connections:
/BOOT0: SW4.2, U4.61 (PB8)
/D+: J1.3 (D+), U1.3 (I/O2)
/D-: J1.2 (D-), U1.1 (I/O1)
/JTCK: J3.9, U4.50 (PA14)
/JTDI: J3.5, U4.51 (PA15)
/JTDO: J3.13, U4.56 (PB3)
/JTMS: J3.7, U4.49 (PA13)
/MCU 3V3: C1.1, C2.1, C4.1, C7.1, C8.1, C9.2, C11.1, C16.1, J3.1, J3.2, L1.1, R1.2, R2.2, U2.5 (VOUT), U3.5 (VIO), U3.6 (VDD), U3.7 (REGIN), U4.16 (VDD), U4.32 (VDD), U4.48 (VDD), U4.64 (VDD)
/MCU_VDDA: C3.1, C5.1, L1.2, U4.1 (VBAT), U4.28 (VREF+), U4.29 (VDDA)
/NJTRST: J3.3, U4.57 (PB4)
/NRST: C12.1, CR1.1, J3.15, SW2.1, U4.7 (PG10)
/PA8: J6.3, U4.42 (PA8)
/PA9: J6.4, U4.43 (PA9)
/PC6: J4.1, U4.38 (PC6)
/UART VBUS: D1.2 (K), J2.1 (VBUS), SW1.1 (A), U3.8 (VBUS)
/UART_CTS: U3.18 (~CTS), U4.12 (PA0)
/UART_D+: D1.4 (K), J2.3 (D+), U3.3 (D+)
/UART_D-: D1.3 (K), J2.2 (D-), U3.4 (D-)
/UART_RTS: U3.19 (~RTS), U4.13 (PA1)
/UART_RXD: U3.20 (RXD), U4.14 (PA2)
/UART_TXD: U3.21 (TXD), U4.17 (PA3)
/USB_D+: U1.4 (I/O2), U4.46 (PA12)
/USB_D-: U1.6 (I/O1), U4.45 (PA11)
/USB_VBUS: C6.1, D2.1, J1.1 (VBUS), SW1.3 (C), U1.5 (VBUS)
GND: C1.2, C2.2, C3.2, C4.2, C5.2, C6.2, C7.2, C8.2, C9.1, C10.2, C11.2, C12.2, C13.2, C14.2, C15.2, C16.2, CR1.2, D1.1 (A), D2.2, J1.4 (ID), J1.5 (GND), J1.6 (Shield), J2.4 (ID), J2.5 (GND), J2.6 (Shield), J3.4, J3.6, J3.8, J3.10, J3.12, J3.14, J3.16, J3.18, J3.20, R3.1, SW2.2, U1.2 (GND), U2.2 (GND), U3.2 (GND), U3.25 (GND), U4.15 (VSS), U4.27 (VSSA), U4.31 (VSS), U4.47 (VSS), U4.63 (VSS)
unnamed: J4.2, U4.37 (PB15)
unnamed: J4.3, U4.36 (PB14)
unnamed: J4.4, U4.35 (PB13)
unnamed: J4.5, U4.34 (PB12)
unnamed: J4.6, U4.33 (PB11)
unnamed: J6.1, U4.39 (PC7)
unnamed: J6.2, U4.40 (PC8)
unnamed: C10.1, C14.1, SW1.2 (B), U2.1 (VIN), U2.3 (INH)
unnamed: R3.2, SW3.1 (A)
unnamed: SW3.2 (B), SW4.1
unnamed: R2.1, SW3.3 (C)
unnamed: C15.1, U2.4 (BYP)
unnamed: C13.1, U3.16 (VPP)
unnamed: R1.1, U3.9 (~RST)

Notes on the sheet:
ESD Array recommended by Silicon Labs for CP2104
USB to UART Bridge
5V to 3V3
Direct USB
STM VDD
No external resistors needed for USB peripheral for G4
Same setup used on NUCLEO G4 Board
ESD is according to datasheet for USB FS
STM32 G4 LQFP64
BOOT0
ST-LINK/V2 CONNECTOR (CN3)
NRST
Using USART2 USART1 RTS and CTS are same pins as USB_DP and USB_DM
NOTE: VBAT MAY NEED A DECOUPLING CAP
STM VDDA, VBAT & VREF
UART
Need some kind of diode? NUCLEO has
Finds DSR DTR Circuits & Implement RST once VIO & VDD are set
Necessary Decoupling Capacitors for VDD (Same as NUCLEO)
